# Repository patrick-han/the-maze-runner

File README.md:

# the-maze-runner

The Maze Runner is a project done for ELEC 327 at Rice University. The concept was to create a more interesting implementation of the game where you navigate a ball from start to finish by tilting the maze.

We did this by:

a) Adding servo motors to control the motion of the board

b) Controlling those servos using a wireless joystick controller

The design files for the PCB's and code are included in this repository.

This project was worked on by:

Patrick Han (patrick-han), Chiraag Kaushik (chiraagk7), Tommy Yuan (ty19)

A detailed report for this project can be found in the Documentation folder of this repository.

Here is the associated website with videos!: https://patrick-han.github.io/ee_projects/the-maze-runner.html

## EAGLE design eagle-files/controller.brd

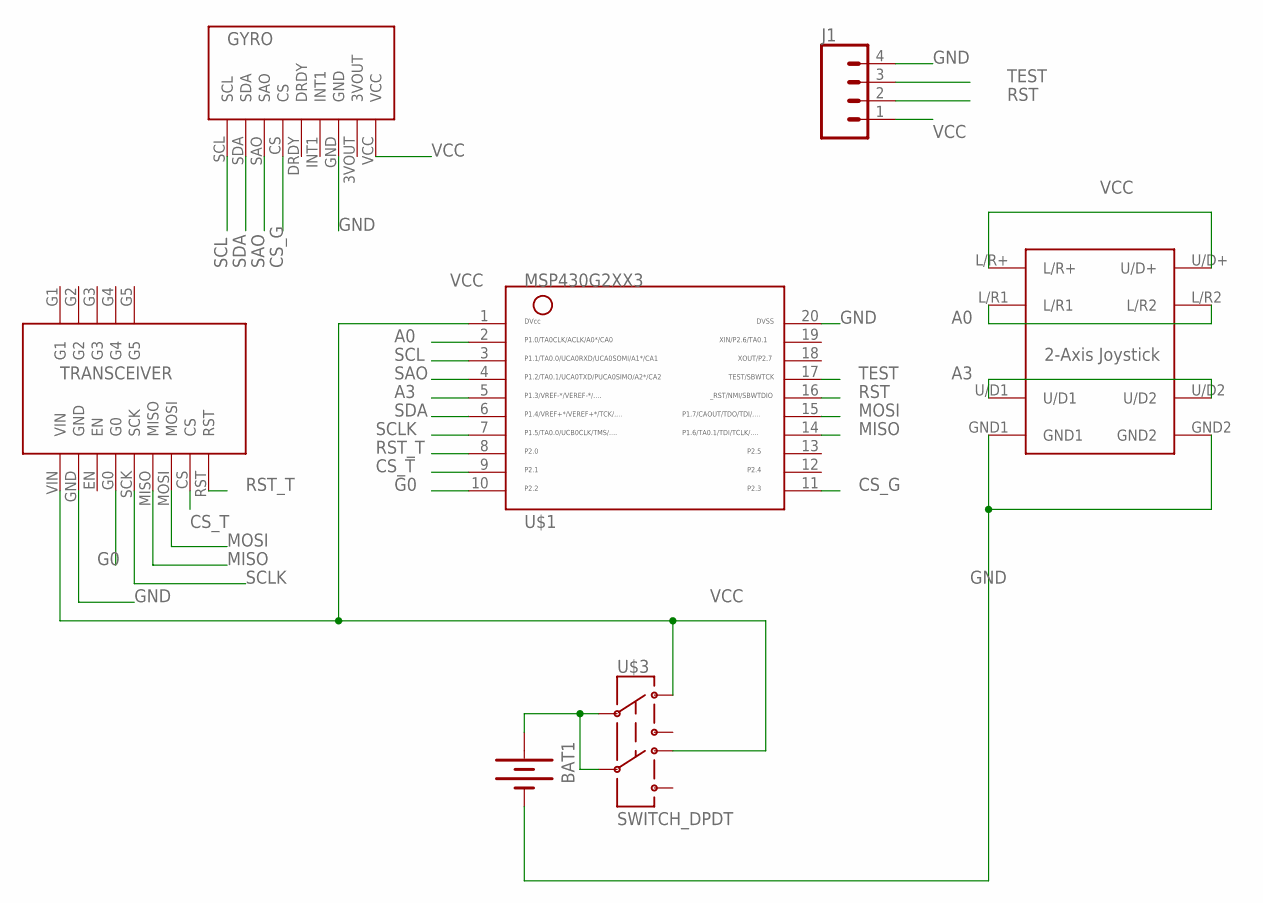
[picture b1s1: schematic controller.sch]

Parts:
BAT1: BATTERY; BATTERY_PACK_2AA
J1: CONN_04LOCK; 1X04_LOCK
U$1: MSP430G2XX3TSSOP; PW20
U$2: PARALLAX-2AXIS-JOYSTICK
U$3: SWITCH_DPDT; JS_DPDT_TH
U$4: ADAFRUIT-RFM69HCW-TRANSCEIVER
U$5: GYRO

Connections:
A0: U$1.2, U$2.L/R1, U$2.L/R2
A3: U$1.5, U$2.U/D1, U$2.U/D2
CS_G: U$1.11, U$5.CS
CS_T: U$1.9, U$4.CS
G0: U$1.10, U$4.G0
GND: BAT1.GND (-), J1.4, U$1.20, U$2.GND1, U$2.GND2, U$4.GND, U$5.GND
MISO: U$1.14, U$4.MISO
MOSI: U$1.15, U$4.MOSI
unnamed: BAT1.3V (+), U$3.2, U$3.5
RST: J1.2, U$1.16
RST_T: U$1.8, U$4.RST
SAO: U$1.4, U$5.SAO
SCL: U$1.3, U$5.SCL
SCLK: U$1.7, U$4.SCK
SDA: U$1.6, U$5.SDA
TEST: J1.3, U$1.17
VCC: J1.1, U$1.1, U$2.L/R+, U$2.U/D+, U$3.1, U$3.4, U$4.VIN, U$5.VCC

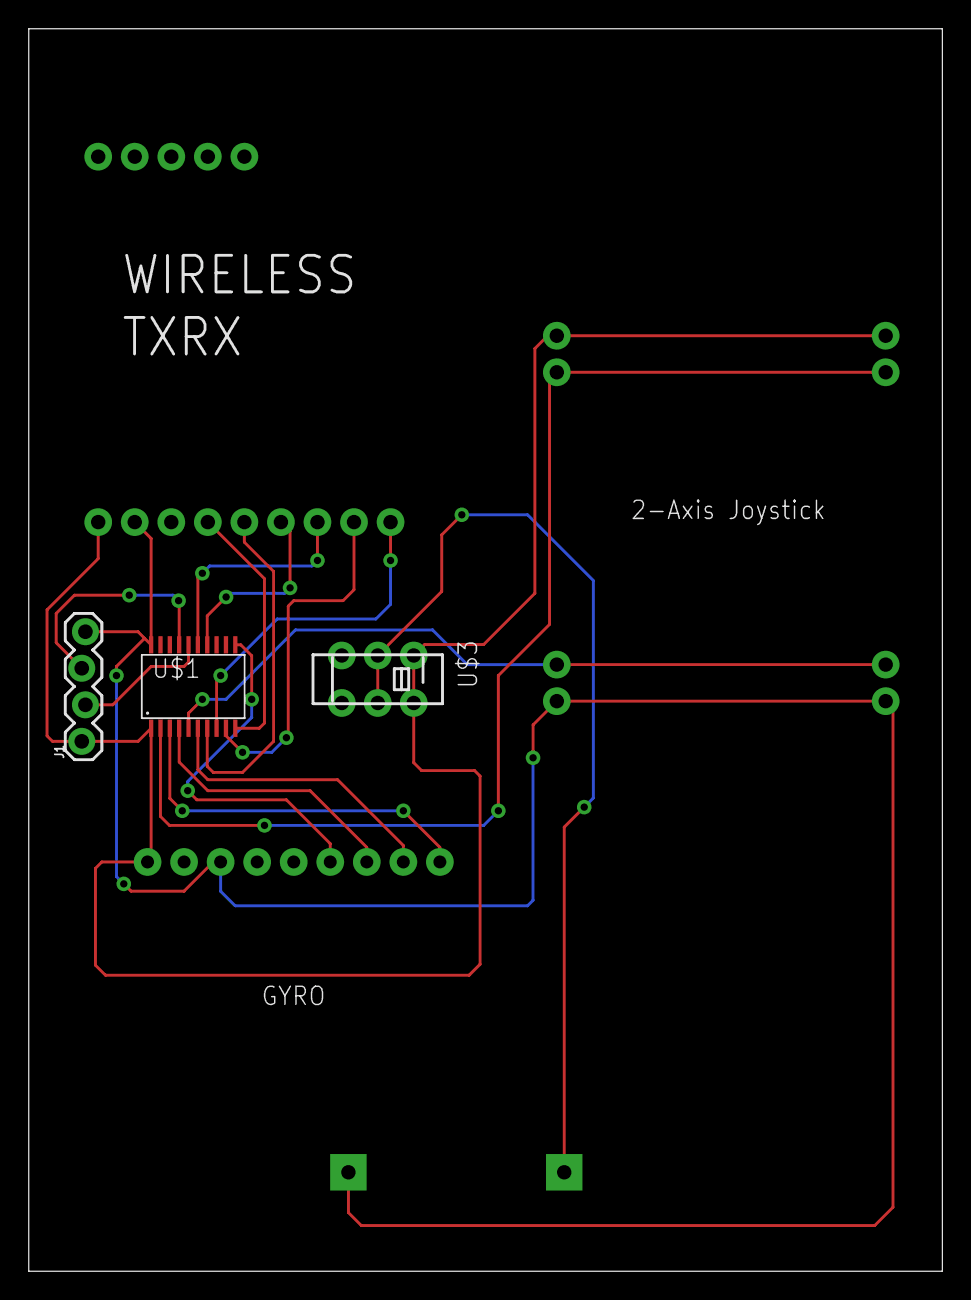
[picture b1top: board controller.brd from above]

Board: 2 copper layers, 63.5 x 86.4 mm, 7 parts (1 on the bottom side), 17 nets.

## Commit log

2019-05-01 added gitignore
2019-05-01 added report
2019-05-01 updated directory structure, added eagle files

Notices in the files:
parts and their libraries:
SparkFun-Connectors: Licensing: Creative Commons ShareAlike 4.0 International - https://creativecommons.org/licenses/by-sa/4.0
